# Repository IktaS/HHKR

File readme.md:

# HHKR

HHKR stands for HHKere, Kere in indonesia means poor. So this is a Poor Man's HHKB PCB, with additional feature such as OLED screen to fill HHKB's empty bottom right space.

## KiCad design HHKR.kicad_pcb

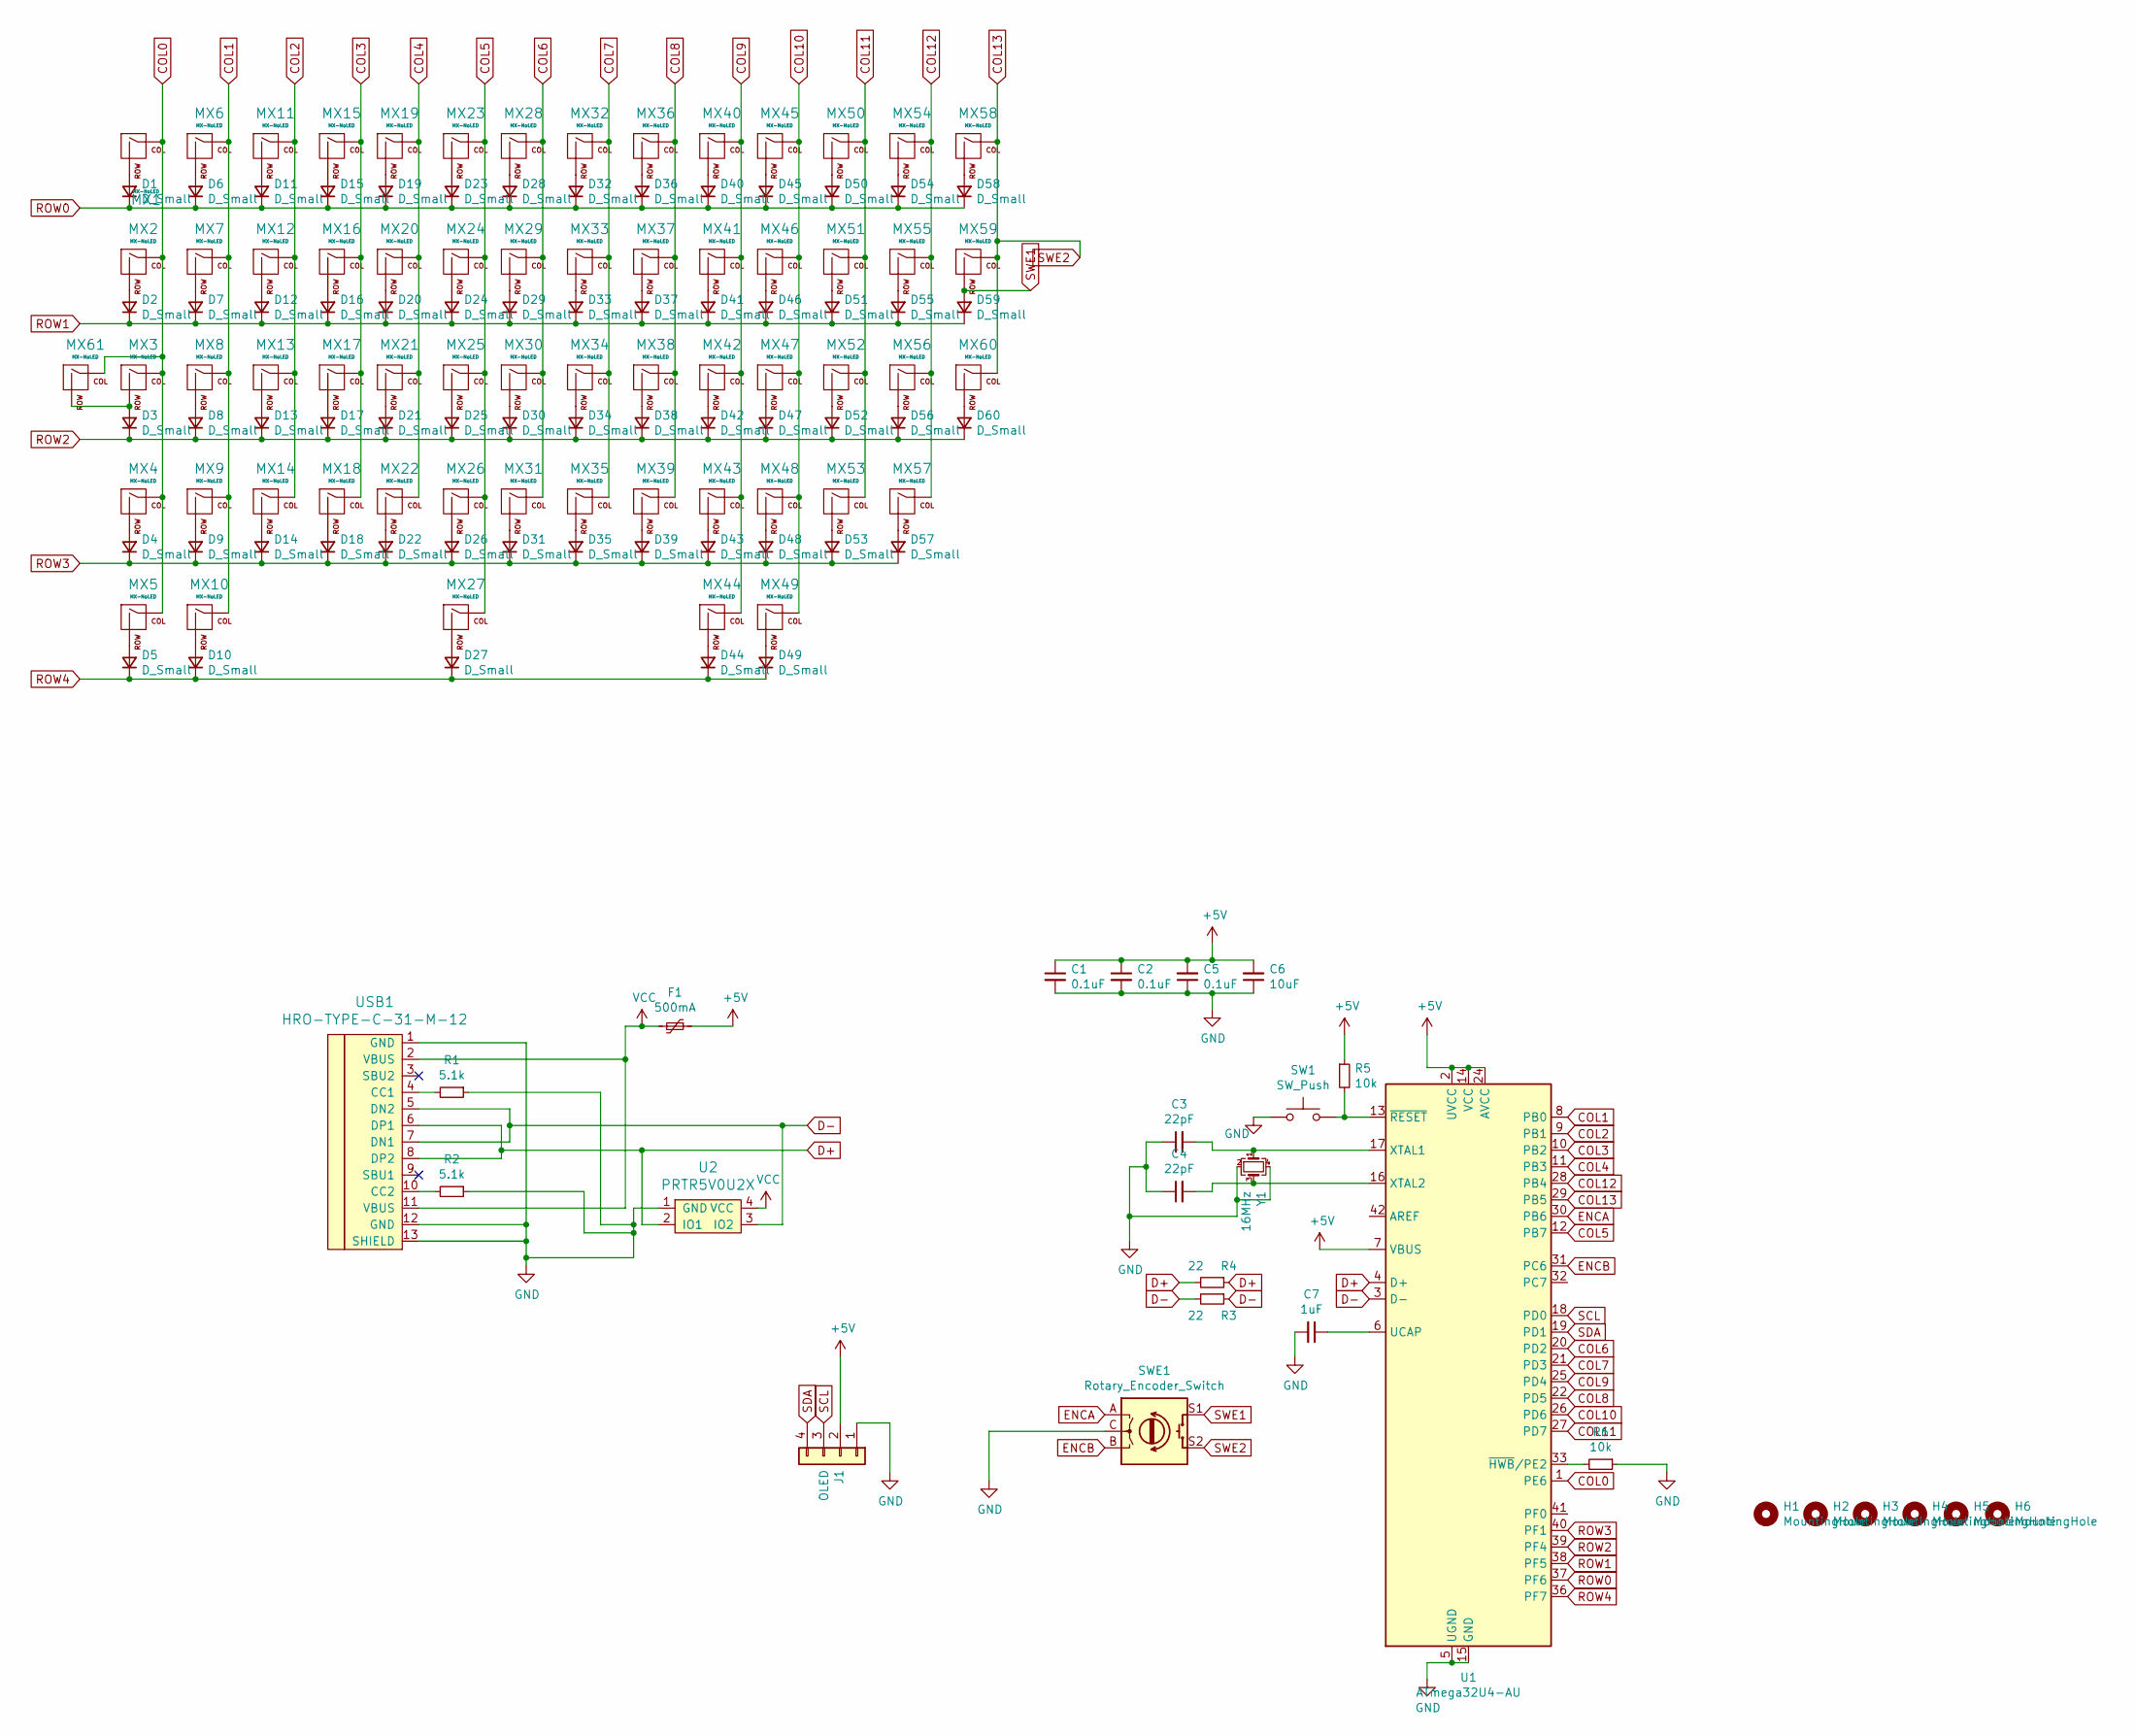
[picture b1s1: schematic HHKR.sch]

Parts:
C1, C2, C5: 0.1uF; C_0805_2012Metric_Pad1.15x1.40mm_HandSolder
C3, C4: 22pF; C_0805_2012Metric_Pad1.15x1.40mm_HandSolder
C6: 10uF; C_0805_2012Metric_Pad1.15x1.40mm_HandSolder
C7: 1uF; C_0805_2012Metric_Pad1.15x1.40mm_HandSolder
D1, D2, D3, D4, D5, D6, D7, D8, D9, D10, D11, D12, D13, D14, D15, D16, D17, D18, D19, D20, D21, D22, D23, D24, D25, D26, D27, D28, D29, D30, D31, D32, D33, D34, D35, D36, D37, D38, D39, D40, D41, D42, D43, D44, D45, D46, D47, D48, D49, D50, D51, D52, D53, D54, D55, D56, D57, D58, D59, D60: D_Small; D_SOD-123-Pretty
F1: 500mA; Fuse_0805_2012Metric_Pad1.15x1.40mm_HandSolder
H1: MountingHole; Generic-Mounthole
H2, H3: MountingHole; HoleVeryWideM2
H4, H5, H6: MountingHole; HoleM2Wide
J1: OLED; PinHeader_1x04_P2.54mm_Vertical
MX1, MX3, MX6, MX61: MX-NoLED; MXOnly-1U-NoLED
MX2, MX5, MX7, MX8, MX9, MX10, MX11, MX12, MX13, MX14, MX15, MX16, MX17, MX18, MX19, MX20, MX21, MX22, MX23, MX24, MX25, MX26, MX28, MX29, MX30, MX31, MX32, MX33, MX34, MX35, MX36, MX37, MX38, MX39, MX40, MX41, MX42, MX43, MX44, MX45, MX46, MX47, MX48, MX49, MX50, MX51, MX52, MX53, MX54, MX55, MX57, MX58, MX59, MX60: MX-NoLED; MXOnly-1U-Hotswap-Antishear
MX4, MX56: MX-NoLED; MXOnly-2.25U-Hotswap-AntiShear
MX27: MX-NoLED; MXOnly-6U-ReversedStabilizers-NoLED-HotSwap-AntiShear
R1, R2: 5.1k; R_0805_2012Metric_Pad1.15x1.40mm_HandSolder
R3, R4: 22; R_0805_2012Metric_Pad1.15x1.40mm_HandSolder
R5, R6: 10k; R_0805_2012Metric_Pad1.15x1.40mm_HandSolder
SW1: SW_Push; SW_SPST_TL3342
SWE1: Rotary_Encoder_Switch; RotaryEncoder_Alps_EC11E-Switch_Vertical_H20mm
U1: ATmega32U4-AU; TQFP-44_10x10mm_P0.8mm
U2: PRTR5V0U2X; SOT143B
USB1: HRO-TYPE-C-31-M-12; HRO-TYPE-C-31-M-12-HandSoldering
Y1: 16MHz; Crystal_SMD_3225-4Pin_3.2x2.5mm_HandSoldering

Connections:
+5V: C1.1, C2.1, C5.2, C6.2, F1.1, J1.2, R5.1, U1.2 (UVCC), U1.7 (VBUS), U1.14 (VCC), U1.24 (AVCC), U1.34 (VCC), U1.44 (AVCC)
COL0: MX1.1 (COL), MX2.1 (COL), MX3.1 (COL), MX4.1 (COL), MX5.1 (COL), MX61.1 (COL), U1.1 (PE6)
COL1: MX6.1 (COL), MX7.1 (COL), MX8.1 (COL), MX9.1 (COL), MX10.1 (COL), U1.8 (PB0)
COL2: MX11.1 (COL), MX12.1 (COL), MX13.1 (COL), MX14.1 (COL), U1.9 (PB1)
COL3: MX15.1 (COL), MX16.1 (COL), MX17.1 (COL), MX18.1 (COL), U1.10 (PB2)
COL4: MX19.1 (COL), MX20.1 (COL), MX21.1 (COL), MX22.1 (COL), U1.11 (PB3)
COL5: MX23.1 (COL), MX24.1 (COL), MX25.1 (COL), MX26.1 (COL), MX27.1 (COL), U1.12 (PB7)
COL6: MX28.1 (COL), MX29.1 (COL), MX30.1 (COL), MX31.1 (COL), U1.20 (PD2)
COL7: MX32.1 (COL), MX33.1 (COL), MX34.1 (COL), MX35.1 (COL), U1.21 (PD3)
COL8: MX36.1 (COL), MX37.1 (COL), MX38.1 (COL), MX39.1 (COL), U1.22 (PD5)
COL9: MX40.1 (COL), MX41.1 (COL), MX42.1 (COL), MX43.1 (COL), MX44.1 (COL), U1.25 (PD4)
COL10: MX45.1 (COL), MX46.1 (COL), MX47.1 (COL), MX48.1 (COL), MX49.1 (COL), U1.26 (PD6)
COL11: MX50.1 (COL), MX51.1 (COL), MX52.1 (COL), MX53.1 (COL), U1.27 (PD7)
COL12: MX54.1 (COL), MX55.1 (COL), MX56.1 (COL), MX57.1 (COL), U1.28 (PB4)
COL13: MX58.1 (COL), MX59.1 (COL), MX60.1 (COL), SWE1.S2, U1.29 (PB5)
D+: R3.1, R3.2, U1.4 (D+), U2.2 (IO1), USB1.6 (DP1), USB1.8 (DP2)
D-: R4.1, R4.2, U1.3 (D-), U2.3 (IO2), USB1.5 (DN2), USB1.7 (DN1)
ENCA: SWE1.A, U1.30 (PB6)
ENCB: SWE1.B, U1.31 (PC6)
GND: C1.2, C2.2, C3.1, C4.1, C5.1, C6.1, C7.2, J1.1, R1.1, R2.1, R6.1, SW1.1, SWE1.C, U1.5 (UGND), U1.15 (GND), U1.23 (GND), U1.35 (GND), U1.43 (GND), U2.1 (GND), USB1.1 (GND), USB1.12 (GND), USB1.13 (SHIELD), Y1.2, Y1.4
unnamed: C3.2, U1.17 (XTAL1), Y1.1
unnamed: C4.2, U1.16 (XTAL2), Y1.3
unnamed: C7.1, U1.6 (UCAP)
unnamed: D1.2 (A), MX1.2 (ROW)
unnamed: D2.2 (A), MX2.2 (ROW)
unnamed: D3.2 (A), MX3.2 (ROW), MX61.2 (ROW)
unnamed: D4.2 (A), MX4.2 (ROW)
unnamed: D5.2 (A), MX5.2 (ROW)
unnamed: D6.2 (A), MX6.2 (ROW)
unnamed: D7.2 (A), MX7.2 (ROW)
unnamed: D8.2 (A), MX8.2 (ROW)
unnamed: D9.2 (A), MX9.2 (ROW)
unnamed: D10.2 (A), MX10.2 (ROW)
unnamed: D11.2 (A), MX11.2 (ROW)
unnamed: D12.2 (A), MX12.2 (ROW)
unnamed: D13.2 (A), MX13.2 (ROW)
unnamed: D14.2 (A), MX14.2 (ROW)
unnamed: D15.2 (A), MX15.2 (ROW)
unnamed: D16.2 (A), MX16.2 (ROW)
unnamed: D17.2 (A), MX17.2 (ROW)
unnamed: D18.2 (A), MX18.2 (ROW)
unnamed: D19.2 (A), MX19.2 (ROW)
unnamed: D20.2 (A), MX20.2 (ROW)
unnamed: D21.2 (A), MX21.2 (ROW)
unnamed: D22.2 (A), MX22.2 (ROW)
unnamed: D23.2 (A), MX23.2 (ROW)
unnamed: D24.2 (A), MX24.2 (ROW)
unnamed: D25.2 (A), MX25.2 (ROW)
unnamed: D26.2 (A), MX26.2 (ROW)
unnamed: D27.2 (A), MX27.2 (ROW)
unnamed: D28.2 (A), MX28.2 (ROW)
unnamed: D29.2 (A), MX29.2 (ROW)
unnamed: D30.2 (A), MX30.2 (ROW)
unnamed: D31.2 (A), MX31.2 (ROW)
unnamed: D32.2 (A), MX32.2 (ROW)
unnamed: D33.2 (A), MX33.2 (ROW)
unnamed: D34.2 (A), MX34.2 (ROW)
unnamed: D35.2 (A), MX35.2 (ROW)
unnamed: D36.2 (A), MX36.2 (ROW)
unnamed: D37.2 (A), MX37.2 (ROW)
unnamed: D38.2 (A), MX38.2 (ROW)
unnamed: D39.2 (A), MX39.2 (ROW)
unnamed: D40.2 (A), MX40.2 (ROW)
unnamed: D41.2 (A), MX41.2 (ROW)
unnamed: D42.2 (A), MX42.2 (ROW)
unnamed: D43.2 (A), MX43.2 (ROW)
unnamed: D44.2 (A), MX44.2 (ROW)
unnamed: D45.2 (A), MX45.2 (ROW)
unnamed: D46.2 (A), MX46.2 (ROW)
unnamed: D47.2 (A), MX47.2 (ROW)
unnamed: D48.2 (A), MX48.2 (ROW)
unnamed: D49.2 (A), MX49.2 (ROW)
unnamed: D50.2 (A), MX50.2 (ROW)
unnamed: D51.2 (A), MX51.2 (ROW)
unnamed: D52.2 (A), MX52.2 (ROW)
unnamed: D53.2 (A), MX53.2 (ROW)
unnamed: D54.2 (A), MX54.2 (ROW)
unnamed: D55.2 (A), MX55.2 (ROW)
unnamed: D56.2 (A), MX56.2 (ROW)
unnamed: D57.2 (A), MX57.2 (ROW)
unnamed: D58.2 (A), MX58.2 (ROW)
unnamed: D60.2 (A), MX60.2 (ROW)
unnamed: R1.2, USB1.4 (CC1)
unnamed: R2.2, USB1.10 (CC2)
unnamed: R5.2, SW1.2, U1.13 (~RESET)
unnamed: R6.2, U1.33 (~HWB~/PE2)
ROW0: D1.1 (K), D6.1 (K), D11.1 (K), D15.1 (K), D19.1 (K), D23.1 (K), D28.1 (K), D32.1 (K), D36.1 (K), D40.1 (K), D45.1 (K), D50.1 (K), D54.1 (K), D58.1 (K), U1.37 (PF6)
ROW1: D2.1 (K), D7.1 (K), D12.1 (K), D16.1 (K), D20.1 (K), D24.1 (K), D29.1 (K), D33.1 (K), D37.1 (K), D41.1 (K), D46.1 (K), D51.1 (K), D55.1 (K), D59.1 (K), U1.38 (PF5)
ROW2: D3.1 (K), D8.1 (K), D13.1 (K), D17.1 (K), D21.1 (K), D25.1 (K), D30.1 (K), D34.1 (K), D38.1 (K), D42.1 (K), D47.1 (K), D52.1 (K), D56.1 (K), D60.1 (K), U1.39 (PF4)
ROW3: D4.1 (K), D9.1 (K), D14.1 (K), D18.1 (K), D22.1 (K), D26.1 (K), D31.1 (K), D35.1 (K), D39.1 (K), D43.1 (K), D48.1 (K), D53.1 (K), D57.1 (K), U1.40 (PF1)
ROW4: D5.1 (K), D10.1 (K), D27.1 (K), D44.1 (K), D49.1 (K), U1.36 (PF7)
SCL: J1.3, U1.18 (PD0)
SDA: J1.4, U1.19 (PD1)
SWE1: D59.2 (A), MX59.2 (ROW), SWE1.S1
VCC: F1.2, U2.4 (VCC), USB1.2 (VBUS), USB1.11 (VBUS)

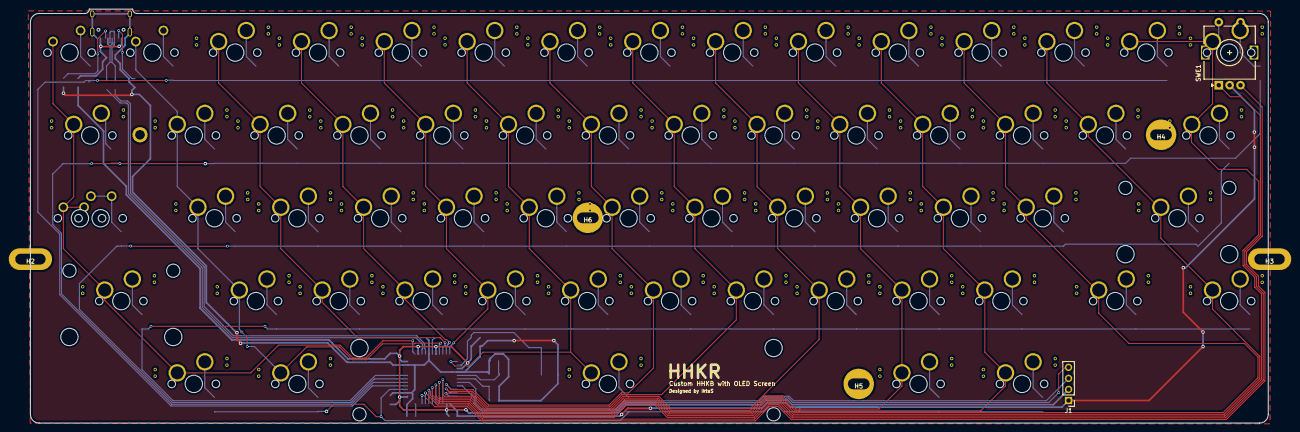
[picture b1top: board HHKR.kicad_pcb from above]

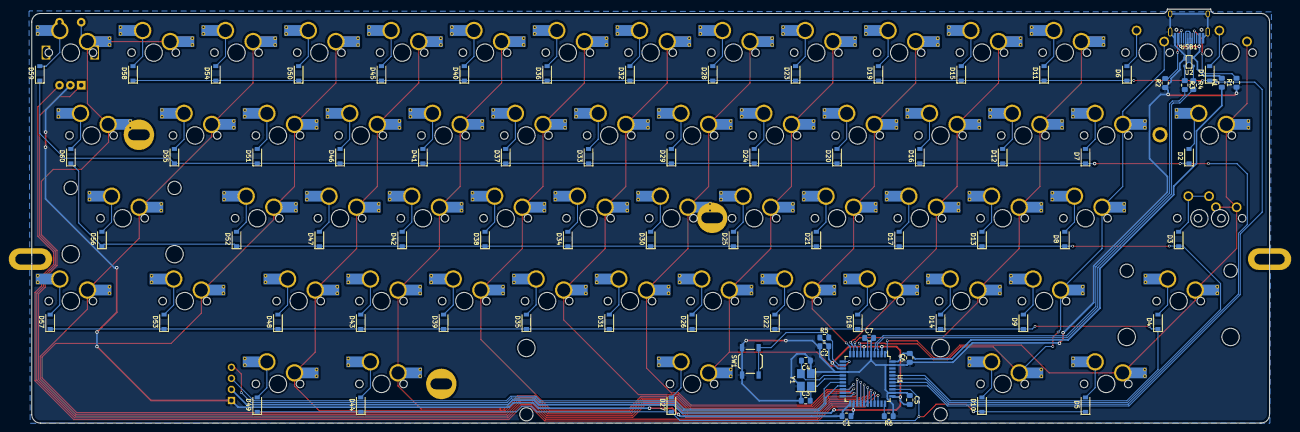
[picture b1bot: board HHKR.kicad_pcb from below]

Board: 2 copper layers, 284.7 x 95.2 mm, 148 parts (79 on the bottom side), 95 nets.

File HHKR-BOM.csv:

"Id";"Designator";"Package";"Quantity";"Designation";"Supplier and ref";
1;"MX60,MX30,MX22,MX18,MX17,MX16,MX59,MX58,MX57,MX55,MX54,MX53,MX52,MX51,MX50,MX49,MX48,MX47,MX46,MX45,MX44,MX43,MX42,MX41,MX40,MX39,MX38,MX37,MX36,MX35,MX34,MX33,MX32,MX31,MX29,MX28,MX26,MX25,MX24,MX23,MX21,MX20,MX19,MX15,MX14,MX13,MX12,MX11,MX10,MX9,MX8,MX7,MX5,MX2";"MXOnly-1U-Hotswap-Antishear";54;"MX-NoLED";;;
2;"H6,H5,H4";"HoleM2Wide";3;"MountingHole";;;
3;"H3,H2";"HoleVeryWideM2";2;"MountingHole";;;
4;"H1";"Generic-Mounthole";1;"MountingHole";;;
5;"MX27";"MXOnly-6U-ReversedStabilizers-NoLED-HotSwap-AntiShear";1;"MX-NoLED";;;
6;"R5,R6";"R_0805_2012Metric_Pad1.15x1.40mm_HandSolder";2;"10k";;;
7;"C2,C1,C5";"C_0805_2012Metric_Pad1.15x1.40mm_HandSolder";3;"0.1uF";;;
8;"C4,C3";"C_0805_2012Metric_Pad1.15x1.40mm_HandSolder";2;"22pF";;;
9;"Y1";"Crystal_SMD_3225-4Pin_3.2x2.5mm_HandSoldering";1;"16MHz";;;
10;"SW1";"SW_SPST_TL3342";1;"SW_Push";;;
11;"C7";"C_0805_2012Metric_Pad1.15x1.40mm_HandSolder";1;"1uF";;;
12;"C6";"C_0805_2012Metric_Pad1.15x1.40mm_HandSolder";1;"10uF";;;
13;"R1,R2";"R_0805_2012Metric_Pad1.15x1.40mm_HandSolder";2;"5.1k";;;
14;"U2";"SOT143B";1;"PRTR5V0U2X";;;
15;"F1";"Fuse_0805_2012Metric_Pad1.15x1.40mm_HandSolder";1;"500mA";;;
16;"MX61,MX3,MX6,MX1";"MXOnly-1U-NoLED";4;"MX-NoLED";;;
17;"MX4,MX56";"MXOnly-2.25U-Hotswap-AntiShear";2;"MX-NoLED";;;
18;"D16,D60,D59,D58,D57,D56,D55,D54,D53,D52,D51,D50,D49,D48,D47,D46,D45,D44,D43,D42,D41,D40,D39,D38,D37,D36,D35,D34,D33,D32,D31,D30,D29,D28,D27,D26,D25,D24,D23,D22,D21,D20,D19,D18,D17,D15,D14,D13,D12,D11,D10,D9,D8,D7,D6,D5,D4,D3,D2,D1";"D_SOD-123-Pretty";60;"D_Small";;;
19;"USB1";"HRO-TYPE-C-31-M-12-HandSoldering";1;"HRO-TYPE-C-31-M-12";;;
20;"U1";"TQFP-44_10x10mm_P0.8mm";1;"ATmega32U4-AU";;;
21;"SWE1";"RotaryEncoder_Alps_EC11E-Switch_Vertical_H20mm";1;"Rotary_Encoder_Switch";;;
22;"R4,R3";"R_0805_2012Metric_Pad1.15x1.40mm_HandSolder";2;"22";;;
23;"J1";"PinHeader_1x04_P2.54mm_Vertical";1;"OLED";;;

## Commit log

2020-09-13 init
2020-09-13 submodules
2020-09-28 v1 gerber
2020-10-01 readme
2020-10-01 readme images
